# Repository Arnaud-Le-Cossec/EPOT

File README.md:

# PROJET EPOT

Réalisé par
Arnaud LE COSSEC
Axel NOUY

Session hiver 2023 - Collège Lionel Groulx

Qu'est-ce que EPOT ?

EPOT est un projet réalisé dans le cadre de la session hiver 2023 au collège Lionel Groulx. L'objectif du projet est de permettre à tout le monde faire pousser ses propres plantes chez soi sans avoir la main verte !

Il s'agit d'un pot de fleur intelligent et connecté, contrôlé par une application mobile. EPOT permet d'automatiser l'arrosage et l'éclairage d'une plante grâce à de nombreux capteurs : capteur d'humidité, de luminosité, de température et de niveau d'eau.

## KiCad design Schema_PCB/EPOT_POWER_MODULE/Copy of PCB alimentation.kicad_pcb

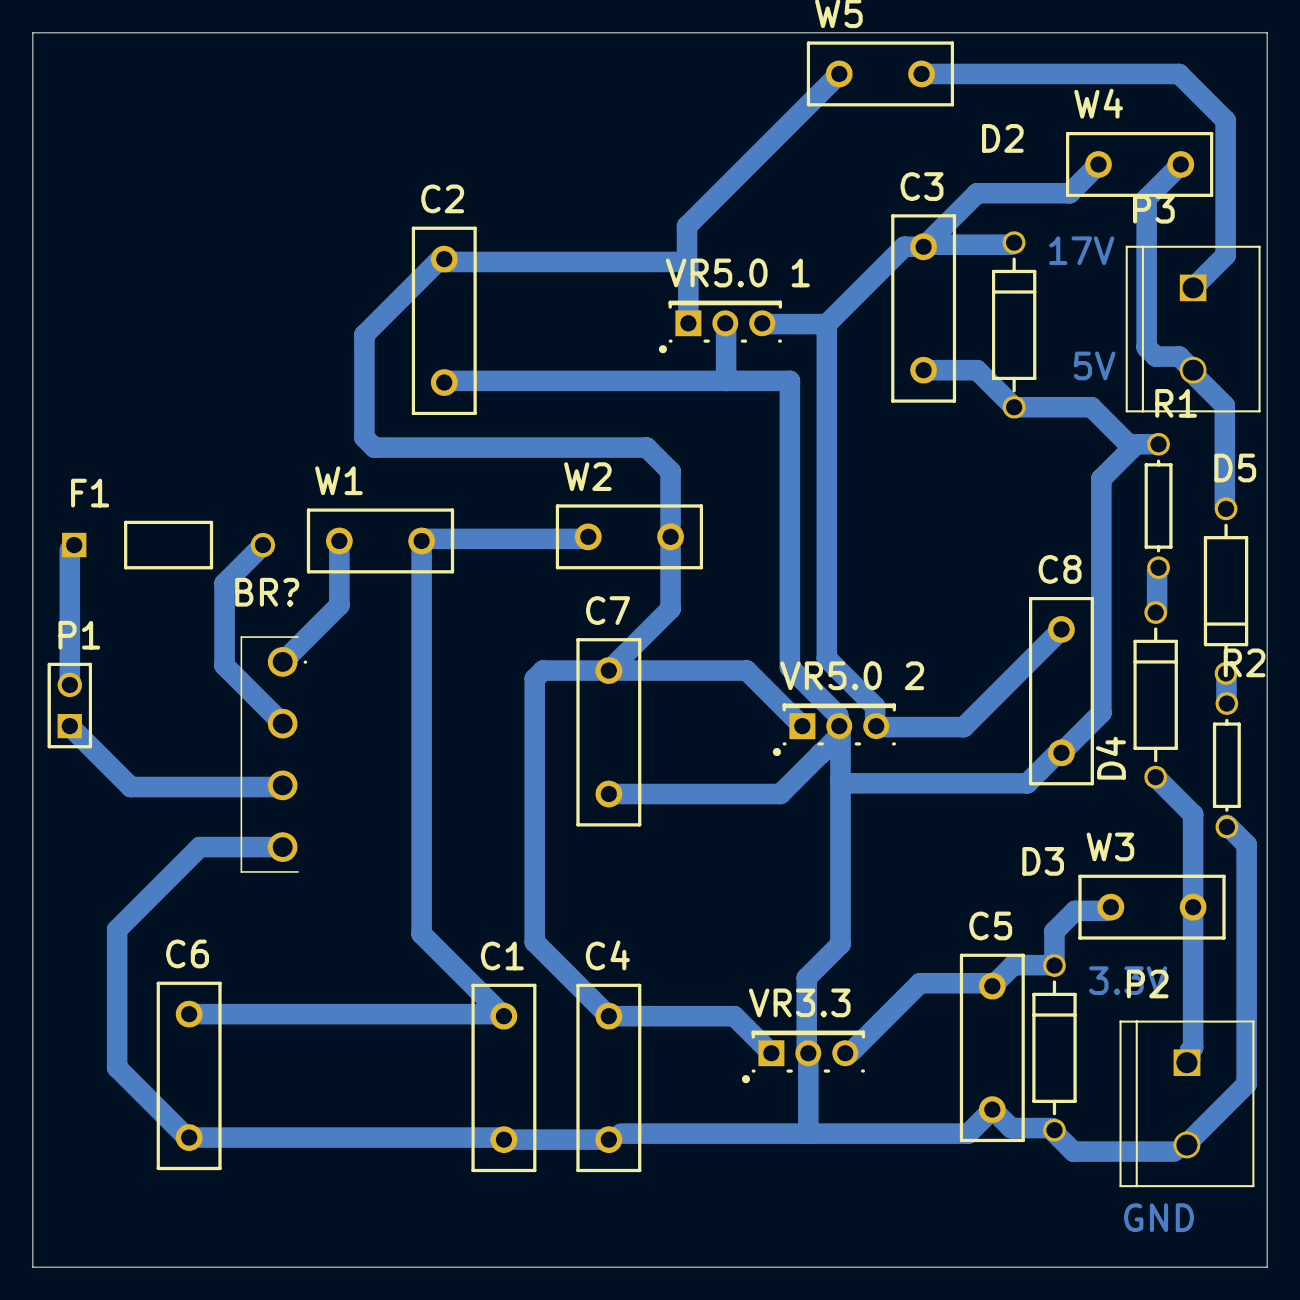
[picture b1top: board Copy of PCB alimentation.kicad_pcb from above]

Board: 2 copper layers, 76.2 x 76.2 mm, 27 parts (0 on the bottom side), 14 nets.

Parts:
BR?: KBP206G
C1, C2, C3, C4, C5, C6, C7, C8: Cap; RAD-0.3
D2, D3: D Zener; DIODE-0.4
D4, D5: Diode; DIODE-0.4
F1: Fuse 1; PIN-W2/E2.8
P1: Header in; HDR1X2
P2: Header out; TE_282837-2
P3: 282837-2; TE_282837-2
R1, R2: Res1; AXIAL-0.3
VR3.3, VR5.0 1, VR5.0 2: Volt Reg; 369-03
W1, W2, W3, W4, W5: Jumper; RAD-0.2

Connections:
GND: BR?.4, C1.1, C2.1, C3.1, C4.1, C5.1, C6.1, C7.1, C8.1, D2.1, D3.1, P2.2, R1.1, R2.1, VR3.3.2, VR5.0 1.2, VR5.0 2.2
NetBR?_1: BR?.1, W1.1
NetBR?_2: BR?.2, F1.2
NetBR?_3: BR?.3, P1.1
NetC1_2: C1.2, C6.2, W1.2, W2.1
NetC2_2: C2.2, C4.2, C7.2, VR3.3.1, VR5.0 1.1, VR5.0 2.1, W2.2, W5.1
NetC3_2: C3.2, C8.2, D2.2, VR5.0 1.3, VR5.0 2.3, W4.1
NetC5_2: C5.2, D3.2, VR3.3.3, W3.1
NetD4_1: D4.1, P2.1, W3.2
NetD4_2: D4.2, R1.2
NetD5_1: D5.1, P3.2, W4.2
NetD5_2: D5.2, R2.2
NetF1_1: F1.1, P1.2
NetP3_1: P3.1, W5.2

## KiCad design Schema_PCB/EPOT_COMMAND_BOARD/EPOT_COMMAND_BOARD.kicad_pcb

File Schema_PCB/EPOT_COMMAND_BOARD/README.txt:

README
Ce dossier contient l'archive du projet KiCAD du module de commande 
Fichier projet : EPOT_COMMAND_BOARD.kicad_pro
Schéma : EPOT_COMMAND_BOARD.kicad_sch
PCB : EPOT_COMMAND_BOARD.kicad_pcb
Paramètres : EPOT_COMMAND_BOARD.kicad_prl

Vous trouverez également une version .png du schéma ainsi qu'une note indiquant les modifications effectuées sur le circuit imprimé.

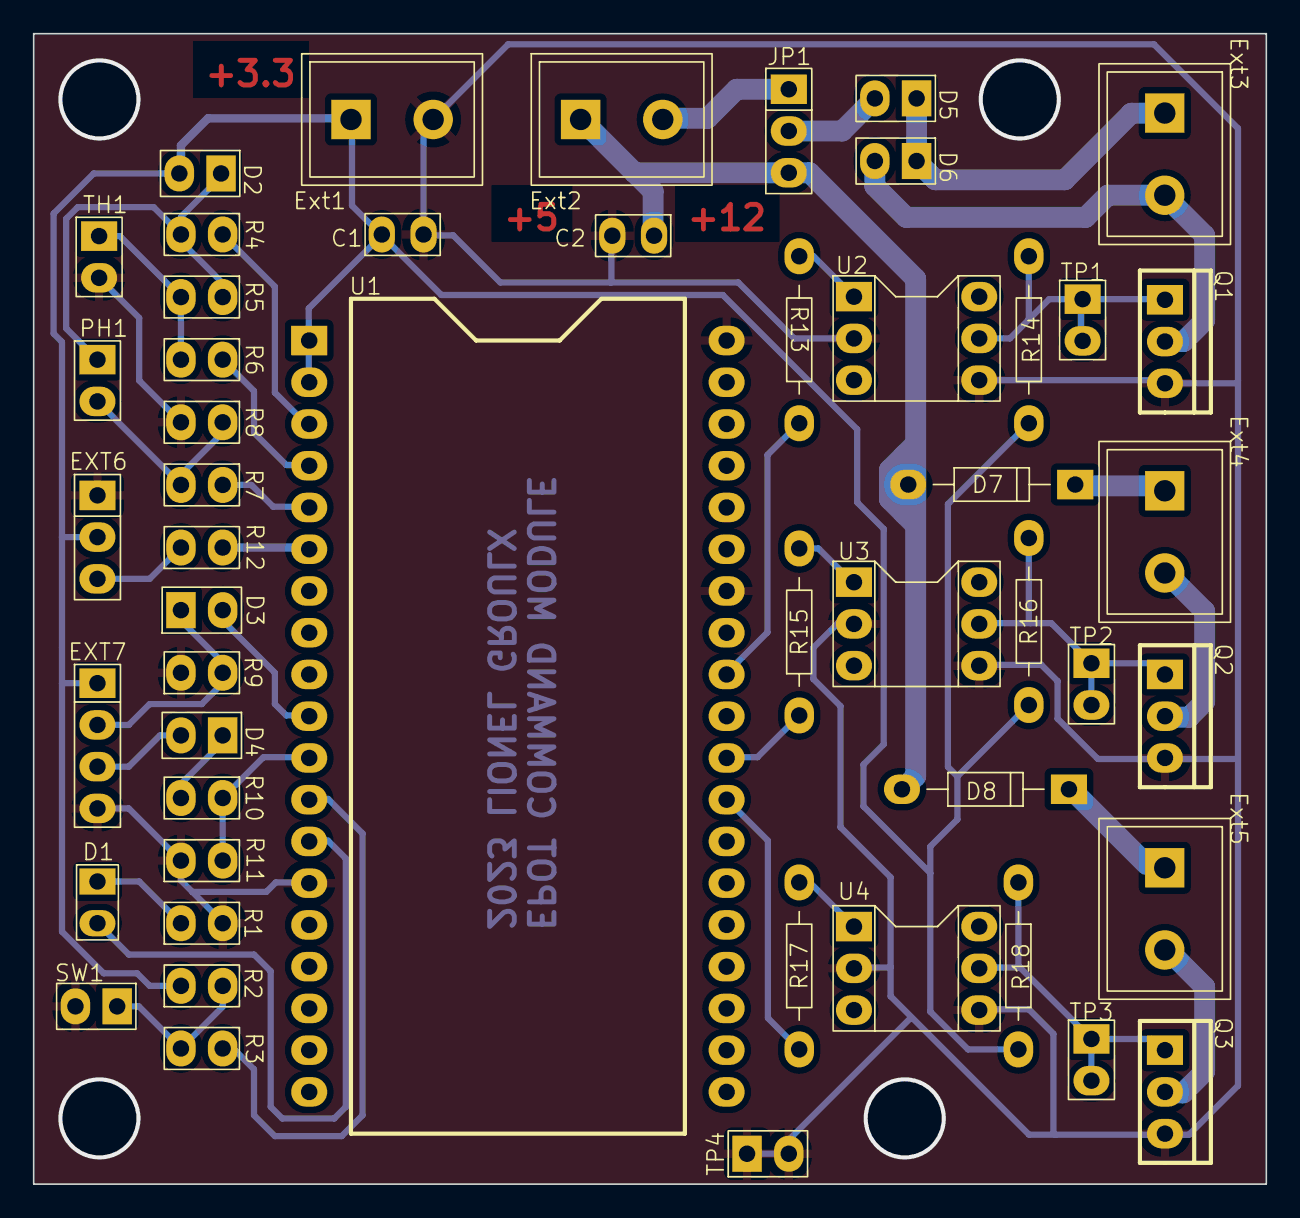
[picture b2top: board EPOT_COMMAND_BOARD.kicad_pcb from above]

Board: 2 copper layers, 75.0 x 70.0 mm, 50 parts (0 on the bottom side), 37 nets.

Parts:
C1, C2: 0.1uF; Unpolarized_capacitor
D1: LED; LED_2.54
D2, D3, D4, D5, D6: 1N4004; Header_2P_2.54
D7, D8: 1N4004; Diode_10.16p
EXT6: Humidity sensor; Header_3P_2.54
EXT7: Ultrasonic_Sensor_HC-SR04; Header_4P_2.54
Ext1, Ext2, Ext3, Ext4, Ext5: TERMINAL BLOCK 2PINS
JP1: Jumper_3_Open; Header_3P_2.54
PH1: R_Photo; Header_2P_2.54
Q1, Q2, Q3: NMOS; TO220
R1, R2, R5, R8: 1k; Vertical_resistor_2.54
R3, R4, R6, R7, R12: 100; Vertical_resistor_2.54
R9, R11: 10k; Vertical_resistor_2.54
R10: 3.7k; Vertical_resistor_2.54
R13, R15, R17: 200; Resistor_10.16p
R14, R16, R18: 10k; Resistor_10.16p
SW1: SW_MEC_5G; Header_2P_2.54
TH1: Thermistor_NTC; Header_2P_2.54
TP1, TP2, TP3, TP4: Header_2P_2.54
U1: ESP32_38P
U2, U3, U4: 4N25; DIP_6_2.54p_7.62w

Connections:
+3.3V: C1.1, D2.2 (A), EXT6.2 (Vcc), EXT7.1 (Vcc), Ext1.1, R2.1, R14.2, R16.2, R18.2, U1.1 (3V3), U1.2 (EN)
+5V: C2.1, D7.2 (A), D8.2 (A), Ext2.1, JP1.3 (B)
+12V: Ext2.2, JP1.1 (A)
/ADC_Top_Ref: R4.1, U1.3 (IO36/A0)
/Humidity_Sensor_Out: R12.2, U1.6 (IO35/A7)
/LED_Control: R15.1, U1.28 (IO17)
/Photo_Out: R7.1, U1.5 (IO34/A6)
/Pump_Control: R13.1, U1.30 (IO18)
/Status_LED: D1.2 (A), U1.13 (IO12/A15)
/Sync_Button: R3.1, U1.12 (IO14/A16)
/Thermistor_Out: R6.1, U1.4 (IO39/A3)
/UV_Control: R17.1, U1.27 (IO16)
/Ultrasonic_Sensor_Echo: R10.1, R11.2, U1.11 (IO27/A17)
/Ultrasonic_Sensor_Trig: D3.2 (A), U1.10 (IO26/A19)
GND: C1.2, C2.2, EXT6.1 (GND), EXT7.4 (GND), Ext1.2, Q1.3 (S), Q2.3 (S), Q3.3 (S), R1.2, R8.2, R9.1, R11.1, SW1.2 (A), TH1.2, TP4.1, TP4.2, U1.14 (GND), U1.32 (GND), U1.38 (GND), U2.2, U2.4, U3.2, U3.4, U4.2, U4.4
unnamed: D1.1 (K), R1.1
unnamed: D2.1 (K), PH1.1, R4.2, R5.1
unnamed: D3.1 (K), EXT7.2 (Trig), R9.2
unnamed: D4.2 (A), EXT7.3 (Echo)
unnamed: D4.1 (K), R10.2
unnamed: D5.2 (A), JP1.2 (C)
unnamed: D5.1 (K), D6.1 (K), Ext3.1
unnamed: D6.2 (A), Ext3.2, Q1.2 (D)
unnamed: D7.1 (K), Ext4.1
unnamed: D8.1 (K), Ext5.1
unnamed: EXT6.3 (Aout), R12.1
unnamed: PH1.2, R7.2, R8.1
unnamed: Q1.1 (G), R14.1, TP1.1, TP1.2, U2.5
unnamed: Ext4.2, Q2.2 (D)
unnamed: Q2.1 (G), R16.1, TP2.1, TP2.2, U3.5
unnamed: Ext5.2, Q3.2 (D)
unnamed: Q3.1 (G), R18.1, TP3.1, TP3.2, U4.5
unnamed: R2.2, R3.2, SW1.1 (A)
unnamed: R5.2, R6.2, TH1.1
unnamed: R13.2, U2.1
unnamed: R15.2, U3.1
unnamed: R17.2, U4.1

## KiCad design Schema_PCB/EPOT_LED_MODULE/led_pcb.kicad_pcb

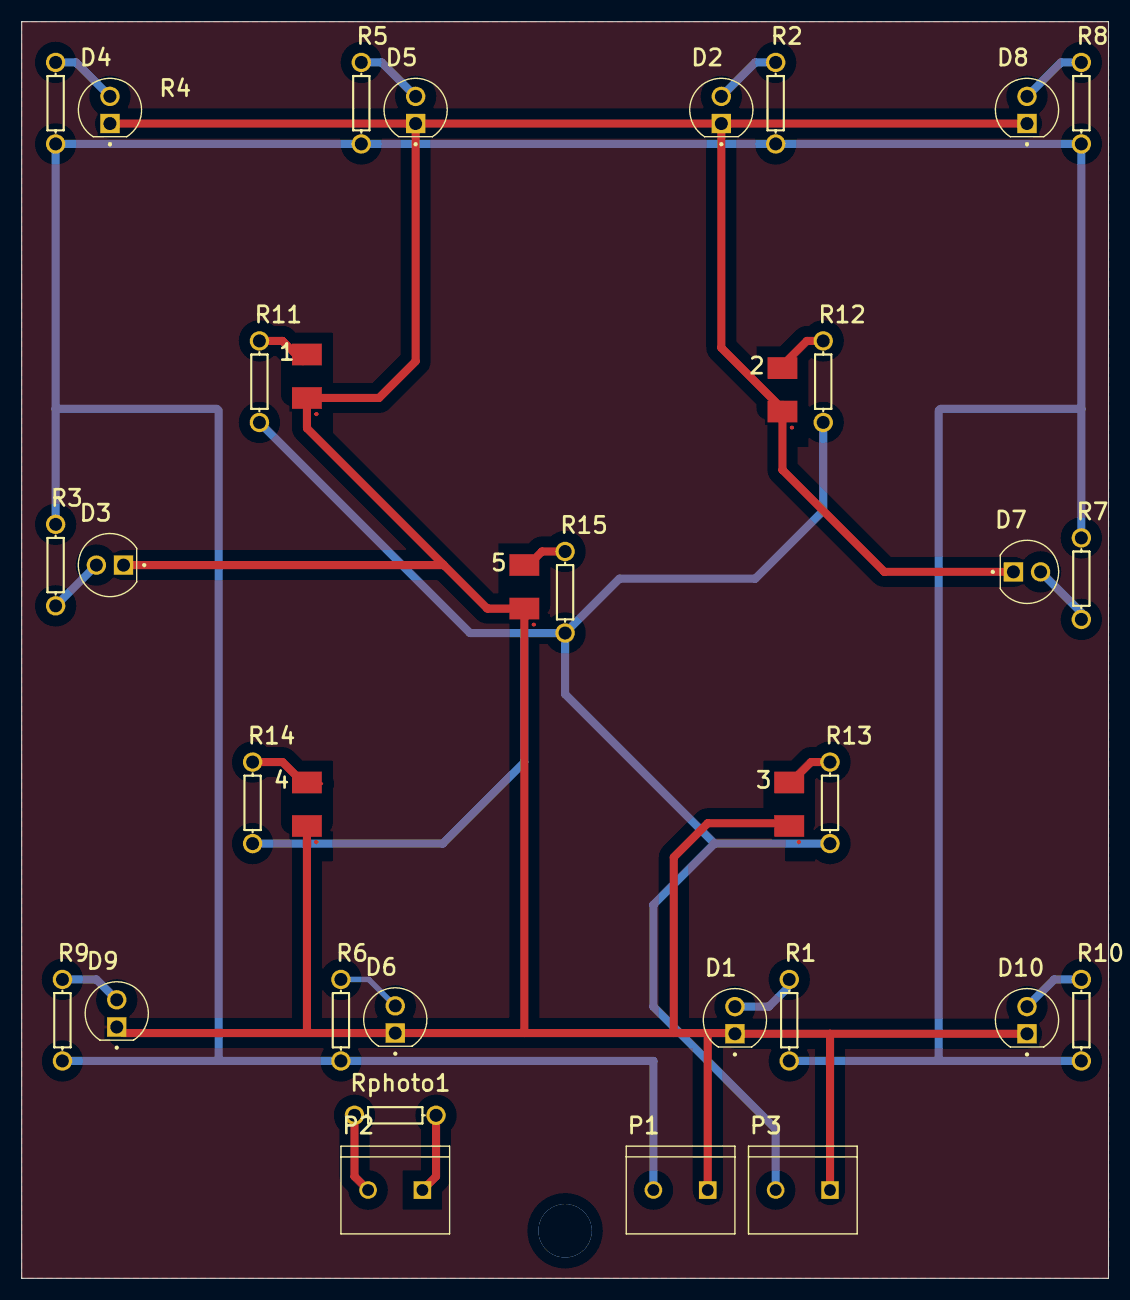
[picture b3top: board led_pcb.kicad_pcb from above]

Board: 2 copper layers, 101.6 x 117.5 mm, 34 parts (0 on the bottom side), 15 nets.

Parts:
1: uv del 1; PCBComponent_1
2: uv del 2; PCBComponent_1
3: uv del 3; PCBComponent_1
4: uv del 4; PCBComponent_1
5: uv del 5; PCBComponent_1
D1, D2, D3, D4, D5, D6, D7, D8, D9, D10: L08R5000Q1; LEDRD254W57D500H1070
P1, P2, P3: 282837-2; TE_282837-2
R1, R2, R3, R4, R5, R6, R7, R8, R9, R10, R11, R12, R13, R14, R15: Res1; AXIAL-0.3
Rphoto1: Res1; AXIAL-0.3

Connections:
GND: 1.1, 2.1, 3.1, 4.1, 5.1, D1.C, D2.C, D3.C, D4.C, D5.C, D6.C, D7.C, D8.C, D9.C, D10.C, P1.1, P3.1
NetD1_A: D1.A, R1.1
NetD2_A: D2.A, R2.1
NetD3_A: D3.A, R3.1
NetD4_A: D4.A, R4.1
NetD5_A: D5.A, R5.1
NetD6_A: D6.A, R6.1
NetD7_A: D7.A, R7.1
NetD8_A: D8.A, R8.1
NetD9_A: D9.A, R9.1
NetD10_A: D10.A, R10.1
NetP1_2: P1.2, R1.2, R2.2, R3.2, R4.2, R5.2, R6.2, R7.2, R8.2, R9.2, R10.2
NetP2_1: P2.1, Rphoto1.2
NetP2_2: P2.2, Rphoto1.1
NetP3_2: P3.2, R11.2, R12.2, R13.2, R14.2, R15.2

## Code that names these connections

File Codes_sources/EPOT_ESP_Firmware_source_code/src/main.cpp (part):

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
  // ------------------ Pin Setup ------------------

  pinMode(LED_CONTROL_PIN, OUTPUT);
  digitalWrite(LED_CONTROL_PIN, HIGH);
  pinMode(UV_CONTROL_PIN, OUTPUT);
  digitalWrite(UV_CONTROL_PIN, HIGH);
  pinMode(PUMP_CONTROL_PIN, OUTPUT);
  digitalWrite(PUMP_CONTROL_PIN, HIGH);

  pinMode(POWER_RELAY, OUTPUT);
  digitalWrite(POWER_RELAY, LOW);
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  if(g_light_manual_auto == MANUAL){    
    // Manual mode
    if(g_light_manual_intensity != last_light_manual_intensity){
      analogWrite(LED_CONTROL_PIN, (255-g_light_manual_intensity*2.5));
      last_light_manual_intensity = g_light_manual_intensity;
    }
  }
  else{
    // Auto mode
    if(g_light_level <= g_light_threshold){ 
      analogWrite(LED_CONTROL_PIN, (255-g_light_manual_intensity*2.5));
    }
    else{
      analogWrite(LED_CONTROL_PIN, 255);
    }
  }

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  if(g_light_manual_auto == MANUAL){ //if(g_UV_manual_auto == MANUAL){ -> UV manual mode is now tied the normal LED manual mode
    // Manual mode
    if(g_UV_manual_intensity != last_UV_manual_intensity){
      analogWrite(UV_CONTROL_PIN, (255-g_UV_manual_intensity*2.5));
      last_UV_manual_intensity = g_UV_manual_intensity;
    }
  }
  else{
    // Auto mode
    if(g_light_level <= g_UV_threshold){
      analogWrite(UV_CONTROL_PIN, (255-g_UV_manual_intensity*2.5));
    }
    else{
      analogWrite(UV_CONTROL_PIN, 255);
    }
  }

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
  if(g_watering_manual_auto == MANUAL){
    // Wattering manual mode
    digitalWrite(PUMP_CONTROL_PIN, !g_pump_manual_on_off); 
  }else
  {
    //Wattering auto mode : if current soil humidity is below the set threshold, 
    //then the pump is activated for 5s every minute to let the soil absorb the water
    if(g_humidity_percentage < g_humidity_threshold){
      if((current_time - last_watering > 60000) && (last_pump_state == STATE_OFF) && (g_water_level_percentage > 5)){
        digitalWrite(PUMP_CONTROL_PIN, STATE_ON);
        last_pump_state = STATE_ON;
        last_watering = current_time;
        Serial.println("ON");
      }
      else if((current_time - last_watering > g_pump_auto_on_time) && (last_pump_state == STATE_ON)){
        digitalWrite(PUMP_CONTROL_PIN, STATE_OFF);
        last_pump_state = STATE_OFF;
        last_watering = current_time;
        Serial.println("OFF");
      }
    }
    else{
      digitalWrite(PUMP_CONTROL_PIN, STATE_OFF);
      last_pump_state = STATE_OFF;
      Serial.println("F OFF");
    }
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
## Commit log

2023-05-05 Create file
2023-05-29 Create RD

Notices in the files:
Codes_sources/EPOT_ESP_Firmware_source_code/src/main.cpp:
(c)2023 Arnaud LE COSSEC
(c)2023 College Lionel Groulx
